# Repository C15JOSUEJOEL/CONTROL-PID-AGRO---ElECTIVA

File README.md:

# CONTROL-PID-AGRO---ELECTIVA
Grupo para CONTROL PID (AGRO)
===============================================================================================
Perspectiva del producto
===============================================================================================
El proyecto se plantea como una herramienta didáctica para facilitar la enseñanza y aplicación práctica del control PID. Su uso principal será en laboratorios de mecatrónica y sistemas de control, donde estudiantes y profesores podrán experimentar con la estabilización de sistemas. Además, se busca que sea portátil, mantenible y adaptable a futuras aplicaciones educativas.

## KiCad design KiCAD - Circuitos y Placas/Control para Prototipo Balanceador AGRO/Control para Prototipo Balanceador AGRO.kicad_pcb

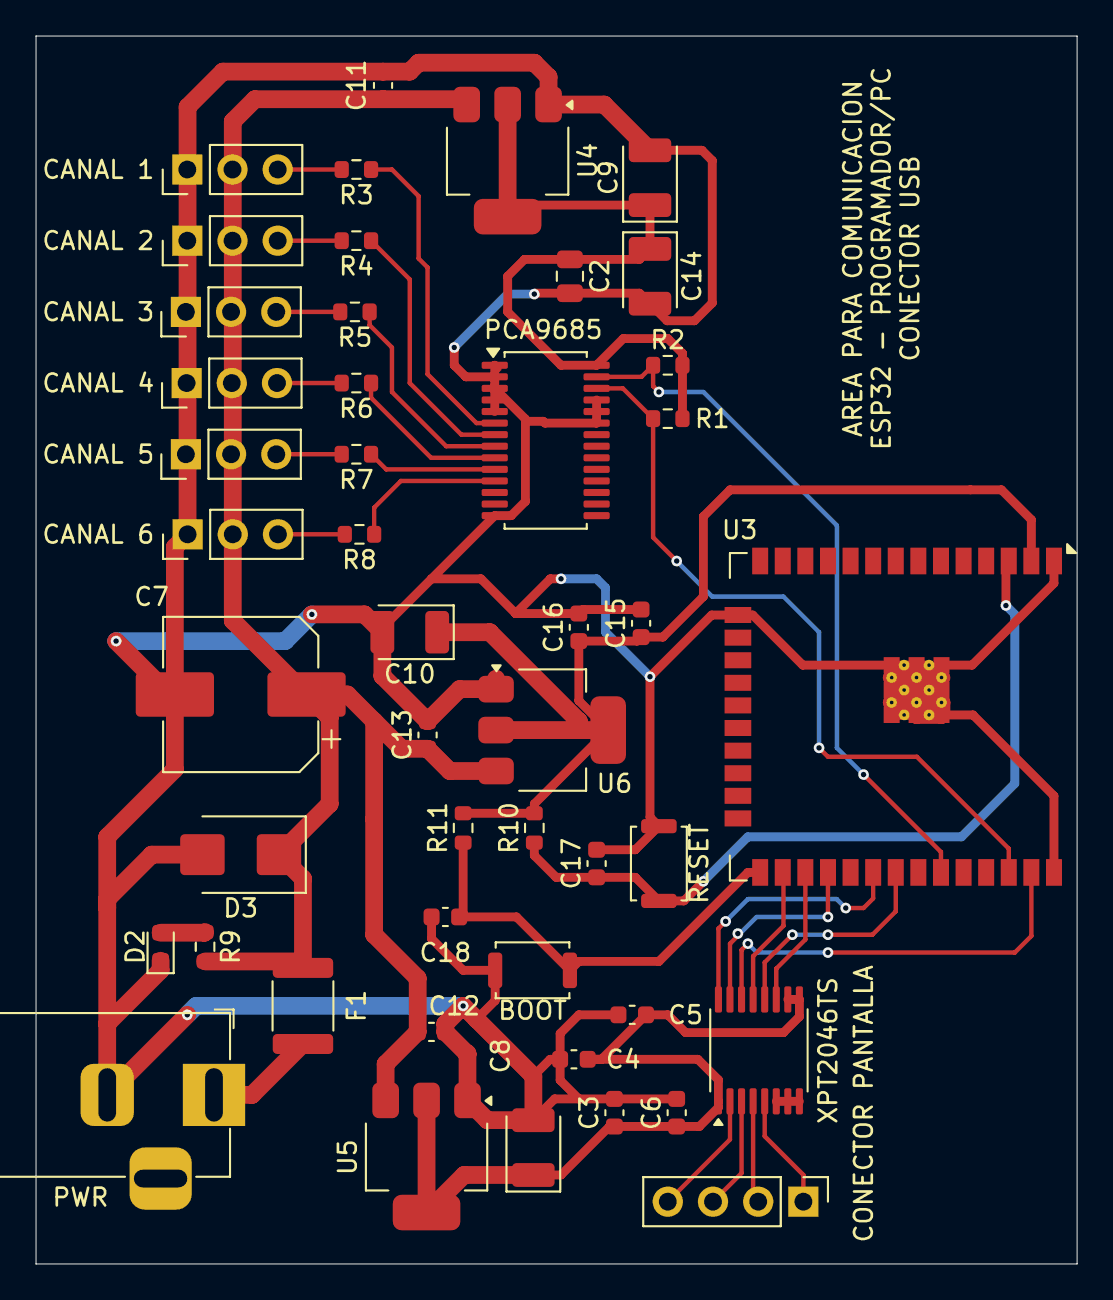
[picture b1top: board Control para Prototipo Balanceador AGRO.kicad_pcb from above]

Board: 2 copper layers, 58.5 x 69.0 mm, 47 parts (0 on the bottom side), 33 nets.

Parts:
BOOT: SW_Push; SW_Push_SPST_NO_Alps_SKRK
C2: 10uF; C_0805_2012Metric
C3, C4, C5, C6, C15, C17, C18: 0.1uF; C_0603_1608Metric
C7: 1000uF; CP_Elec_8x10.5
C8, C9, C10: 22uF; CP_EIA-3528-12_Kemet-T
C11, C12, C13: 22uF; C_0603_1608Metric
C14: 100uF; CP_EIA-3528-12_Kemet-T
C16: 10uF; C_0603_1608Metric
CANAL 1, CANAL 2, CANAL 3, CANAL 4, CANAL 5, CANAL 6: Conn_01x03_Pin; PinHeader_1x03_P2.54mm_Vertical
CONECTOR PANTALLA: Conn_01x04_Pin; PinHeader_1x04_P2.54mm_Vertical
D2: LED; LED_0603_1608Metric
D3: SM6T6V8A; D_SMB
F1: 5A; Fuse_1812_4532Metric
PCA9685: PCA9685PW; TSSOP-28_4.4x9.7mm_P0.65mm
PWR: 5V_15A; BarrelJack_Horizontal
R1, R2: 4.7k; R_0603_1608Metric
R3, R4, R5, R6, R7, R8: 220; R_0603_1608Metric
R9: 1k; R_0603_1608Metric
R10, R11: 10K; R_0603_1608Metric
RESET: SW_Push; SW_Push_SPST_NO_Alps_SKRK
U3: ESP32-WROOM-32E
U4, U5, U6: AMS1117-3.3; SOT-223-3_TabPin2
XPT2046TS: XPT2046TS; TSSOP-16_4.4x5mm_P0.65mm

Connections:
+5V: C7.1, C11.1, C12.1, C13.1, CANAL 1.2, CANAL 2.2, CANAL 3.2, CANAL 4.2, CANAL 5.2, CANAL 6.2, D3.1 (A1), F1.1, R9.2, U4.3 (VI), U5.3 (VI), U6.3 (VI)
GND: BOOT.2, C2.2, C3.2, C4.2, C5.2, C6.2, C7.2, C8.2, C9.2, C10.2, C11.2, C12.2, C13.2, C14.2, C15.2, C16.2, C17.2, C18.2, CANAL 1.1, CANAL 2.1, CANAL 3.1, CANAL 4.1, CANAL 5.1, CANAL 6.1, D2.1 (K), D3.2 (A2), PCA9685.1 (A0), PCA9685.2 (A1), PCA9685.3 (A2), PCA9685.4 (A3), PCA9685.5 (A4), PCA9685.14 (VSS), PCA9685.23 (~OE), PCA9685.24 (A5), PCA9685.25 (EXTCLK), PWR.2, RESET.1, U3.1 (GND), U3.15 (GND), U3.38 (GND), U3.39 (GND), U4.1 (GND), U5.1 (GND), U6.1 (GND), XPT2046TS.6 (GND), XPT2046TS.7 (VBAT), XPT2046TS.8 (IN)
I2C_SCL: PCA9685.26 (SCL), R1.1, U3.36 (IO22)
I2C_SDA: PCA9685.27 (SDA), R2.1, U3.33 (IO21)
MISO: U3.31 (IO19), XPT2046TS.12 (DOUT)
MOSI: U3.37 (IO23), XPT2046TS.14 (DIN)
unnamed: D2.2 (A), R9.1
unnamed: F1.2, PWR.1
unnamed: PCA9685.6 (LED0), R3.1
unnamed: PCA9685.7 (LED1), R4.1
unnamed: PCA9685.8 (LED2), R5.1
unnamed: PCA9685.9 (LED3), R6.1
unnamed: PCA9685.10 (LED4), R7.1
unnamed: PCA9685.11 (LED5), R8.1
unnamed: C17.1, R10.1, RESET.2, U3.3 (EN)
unnamed: BOOT.1, C18.1, R11.1, U3.25 (IO0)
POWER_C_SERVO_3.3V: C2.1, C9.1, C14.1, PCA9685.28 (VDD), R1.2, R2.2, U4.2 (VO)
POWER_ESP32_3.3V: C10.1, C15.1, C16.1, R10.2, R11.2, U3.2 (VDD), U6.2 (VO)
POWER_SCREEN_3.3V: C3.1, C4.1, C5.1, C6.1, C8.1, U5.2 (VO), XPT2046TS.1 (VCC), XPT2046TS.9 (VREF), XPT2046TS.10 (IOVDD)
SCK: U3.30 (IO18), XPT2046TS.16 (DCLK)
SERVO1_SIG: CANAL 1.3, R3.2
SERVO2_SIG: CANAL 2.3, R4.2
SERVO3_SIG: CANAL 3.3, R5.2
SERVO4_SIG: CANAL 4.3, R6.2
SERVO5_SIG: CANAL 5.3, R7.2
SERVO6_SIG: CANAL 6.3, R8.2
TP_BUSY: U3.26 (IO4), XPT2046TS.13 (BUSY)
TP_CS: U3.28 (IO17), XPT2046TS.15 (~CS)
TP_IRQ: U3.27 (IO16), XPT2046TS.11 (~PENIRQ)
X+: CONECTOR PANTALLA.4, XPT2046TS.2 (XP)
X-: CONECTOR PANTALLA.2, XPT2046TS.4 (XN)
Y+: CONECTOR PANTALLA.3, XPT2046TS.3 (YP)
Y-: CONECTOR PANTALLA.1, XPT2046TS.5 (YN)

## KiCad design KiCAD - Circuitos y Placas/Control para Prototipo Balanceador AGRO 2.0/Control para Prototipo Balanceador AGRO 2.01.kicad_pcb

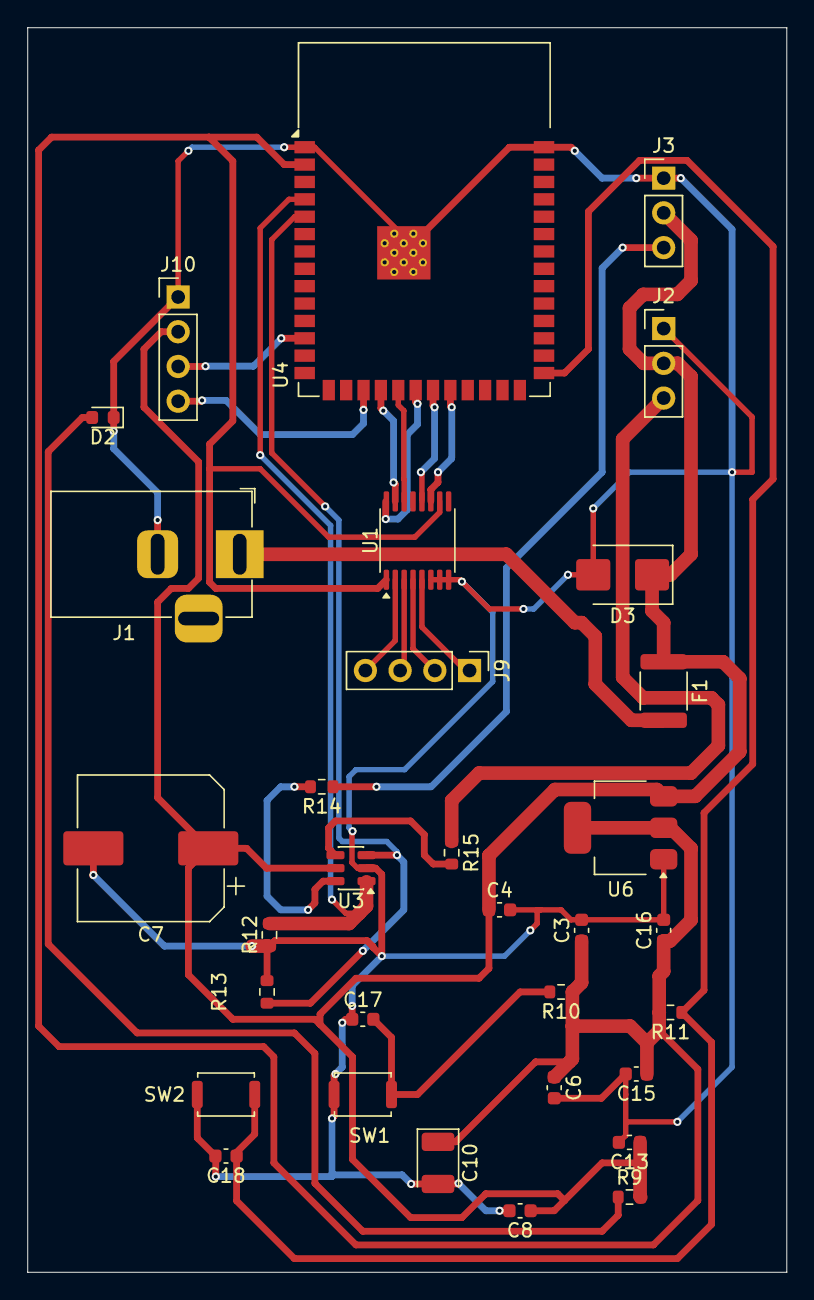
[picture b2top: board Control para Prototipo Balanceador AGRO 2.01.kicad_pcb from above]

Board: 2 copper layers, 55.5 x 91.0 mm, 32 parts (0 on the bottom side), 24 nets.

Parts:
C3, C8, C15, C17, C18: 0.1uF; C_0603_1608Metric
C4, C6, C16: 10uF; C_0603_1608Metric
C7: 1000uF; CP_Elec_10x10.5
C10: 22uF; CP_EIA-3528-21_Kemet-B
C13: 22uF; C_0603_1608Metric
D2: LED; LED_0603_1608Metric
D3: SM6T6V8A; D_SMB
F1: 5A; Fuse_1812_4532Metric
J1: 5V_15A; BarrelJack_Horizontal
J2: Conector_Y; PinHeader_1x03_P2.54mm_Vertical
J3: Conector_X; PinHeader_1x03_P2.54mm_Vertical
J9, J10: Conn_01x04_Pin; PinHeader_1x04_P2.54mm_Vertical
R9: 1k; R_0603_1608Metric
R10, R11, R12, R13: 10K; R_0603_1608Metric
R14, R15: 220; R_0603_1608Metric
SW1, SW2: SW_Push; SW_Push_SPST_NO_Alps_SKRK
U1: TSC2046IPW; TSSOP-16_4.4x5mm_P0.65mm
U3: 74HCT2G34; SOT-23-6
U4: ESP32-S3-WROOM-1
U6: AMS1117-3.3; SOT-223-3_TabPin2

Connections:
+3.3V: C3.1, C6.1, C10.1, C15.1, C16.1, R10.1, R11.2, U1.1 (VCC+), U1.10 (IOVDD), U4.2 (3V3), U6.2 (VO)
+5V: C4.1, C7.1, C8.1, C13.1, D3.1 (A1), F1.1, J2.2, J3.2, J10.2, R9.2, U3.5 (VCC), U6.3 (VI)
CHIP_1A: R12.2, U3.1 (1A), U4.4 (IO4)
CHIP_2A: R13.2, U3.3 (2A), U4.5 (IO5)
ESP_EN: C17.2, R10.2, SW1.1, U4.3 (EN)
ESP_IO0: C18.1, R11.1, SW2.1, U4.27 (IO0)
GND: C3.2, C4.2, C6.2, C7.2, C8.2, C10.2, C13.2, C15.2, C16.2, C17.1, C18.2, D2.1 (K), D3.2 (A2), J1.2, J2.1, J3.1, J10.1, R12.1, R13.1, SW1.2, SW2.2, U1.6 (GND), U1.7 (VBAT), U1.8 (AUX), U3.2 (GND), U4.1 (GND), U4.40 (GND), U4.41 (GND), U6.1 (GND)
I2C_SCL: J10.4, U4.17 (IO9)
I2C_SDA: J10.3, U4.12 (IO8)
MISO: U1.12 (DOUT), U4.21 (IO13)
MOSI: U1.14 (DIN), U4.19 (IO11)
unnamed: D2.2 (A), R9.1
unnamed: F1.2, J1.1
unnamed: R14.2, U3.6 (1Y)
unnamed: R15.2, U3.4 (2Y)
SCK: U1.16 (DCLK), U4.20 (IO12)
Servo_Motor_X_Signal: J3.3, R14.1
Servo_Motor_Y_Signal: J2.3, R15.1
TP_CS: U1.15 (*CS), U4.18 (IO10)
TP_IRQ: U1.11 (*PENIRQ), U4.22 (IO14)
X+: J9.4, U1.2 (X+)
X-: J9.2, U1.4 (X-)
Y+: J9.3, U1.3 (Y+)
Y-: J9.1, U1.5 (Y-)
